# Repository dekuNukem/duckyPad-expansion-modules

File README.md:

# duckyPad Expansion Module

[Pre-order](https://www.kickstarter.com/projects/dekunukem/duckypad-pro-advanced-macro-scripting-beyond-qmk-via) | [Official Discord](https://discord.gg/4sJCBx5) | [Project Page](https://github.com/dekuNukem/duckyPad-Pro) | [Table of Contents](#table-of-contents)

duckyPad Expansion Module lets you wire up external **switches / buttons / foot pedals** to your duckyPad Pro.

* **8 Channels** Per Module

* **Daisy-Chain** up to 32 Channels

* USB-C Connector

## Table of Contents

- [Kit Assembly](#kit-assembly)
- [Connection Overview](#connection-overview)
	- [Terminal Block](#connection-terminal-block)
	- [3.5mm Audio Jack](#connection-35mm-audio-jack)
	- [Pin Headers](#connection-pin-headers)
- [Key Test](#key-test)
- [Configurator](#configurator)

## Kit Assembly

* **Wash your hands first** to discharge static electricity

You should have the following parts:

Insert the `8mm Screws` in `Bottom Plate`:

Place **something rigid** against the back, and flip over.

The screws should stay in place.

Put on **2.5mm Nylon Spacers**.

Insert the `Circuit Board`.

Then the `8mm Metal Spacer`

* **Moderately tighten** with a socket bit if available

* Avoid scratching the PCB or nearby components.

Leave the `Top Plate` off for now.

You can install it after everything is wired up.

## Back to duckyPad!

If you're just starting, **set up your duckyPad first by [following the User Guide](https://dekunukem.github.io/duckyPad-Pro/doc/getting_started.html)**

Play with scripts on built-in switches and encoders, continue here once familiarised.

## Connection Overview

**8 Channels** are available per module.

* Numbered 1 to 8
* A channel is **considered active** when it is **shorted to ground (GND)**.

Therefore, to wire up a switch, you just need to:

* Connect **one side** to **GND**
* And the **other side** to the **desired channel**

---------

You can make connections via:

* Terminal Block
* 3.5mm Jack
* Pin Headers

## Connection: Terminal Block

Take a look at the `terminal block`:

Contains **Channel 1 to 7** and **GND**

To wire up a switch, connect it between a channel and GND.

-------

As an example, here's a simple button with two wires:

* When not pushed, the wires are isolated.
* When pushed, they are **connected together**.

Therefore, we just need to attach one wire to GND, and the other to a channel.

* Flip up the lever for GND and the desired channel

* Strip around half inch / 1.2cm of conductor
* Insert into the hole
* Flip lever back down

## Connection: 3.5mm Audio Jack

Two 3.5mm TRS (Tip, Ring, Sleeve) connectors are available.

Sleeve is connected to GND.

Tip and Ring are connected to channels shown below.

## Connection: Pin Headers

All channels are also available on pin headers.

You can install a header or solder wires directly to them.

## Key Test

Use a USB-C cable and connect the module as shown.

* Make sure the `Towards duckyPad` marking faces duckyPad

* The other end is used for daisy-chaining

Press the `Key Test` script in `Welcome` profile

Press a built-in switch, the screen should respond.

Then activate a channel on the expansion module.

The corresponding LED should light up:

The screen should show too:

If so, congrats! Your wiring is correct.

## Configurator

You can assign actions to expansion channels just like any other key.

Module 1 is closest to duckyPad, up to 4 can be daisy-chained.

Some notes:

* If using a flip switch, select `Disable Auto-Repeat`.
* So the script doesn't repeat after changing state.

* Each channel can have different scripts for `onPress` and `onRelease`.
	* `onPress` is when a channel goes from inactive to active
	* `onRelase` is the opposite

## Questions or Comments?

Please feel free to [open an issue](https://github.com/dekuNukem/duckypad-pro/issues), ask in the [official duckyPad discord](https://discord.gg/4sJCBx5), or email `dekuNukem`@`gmail`.`com`!

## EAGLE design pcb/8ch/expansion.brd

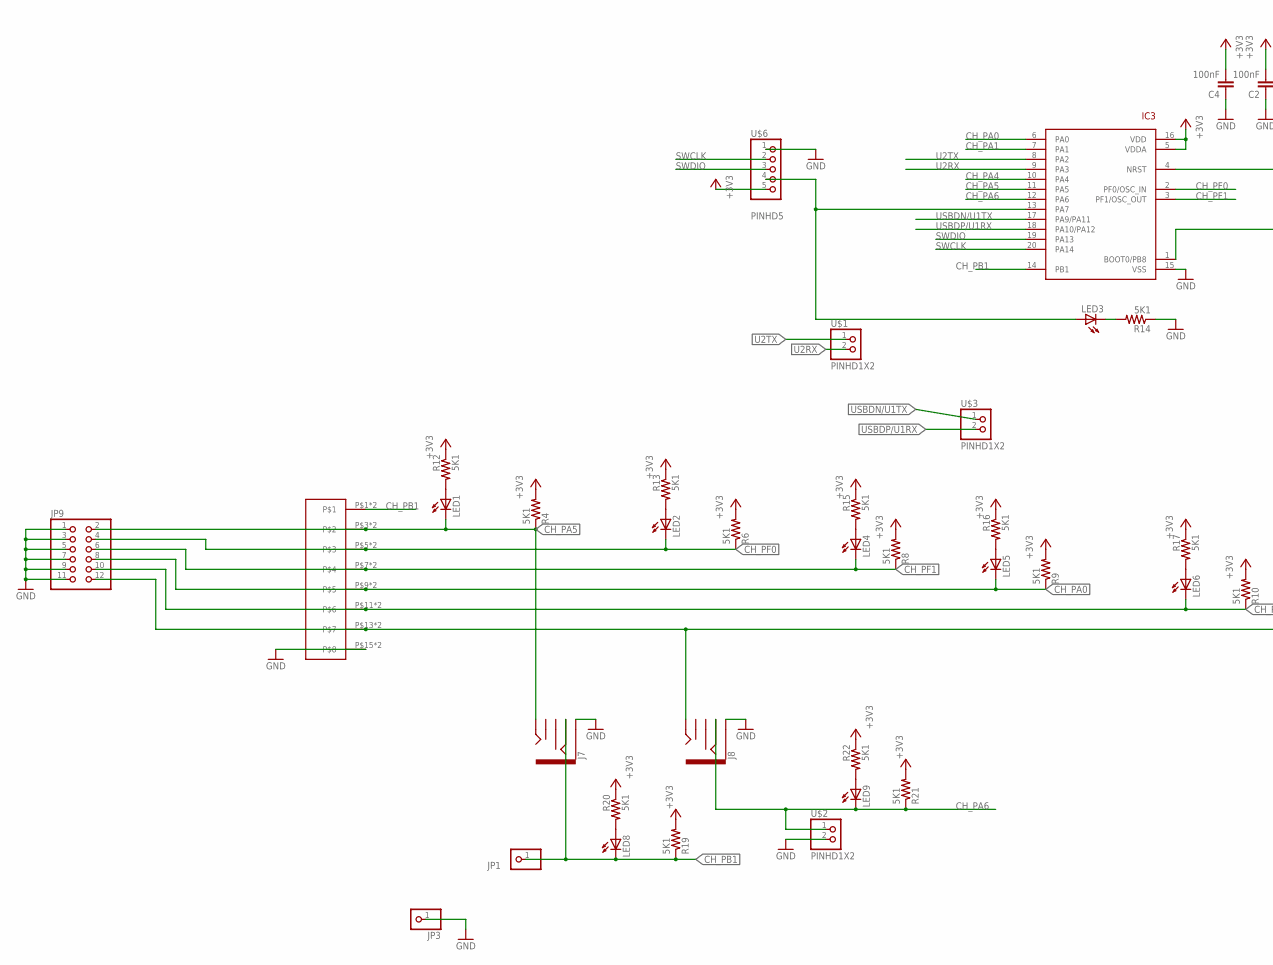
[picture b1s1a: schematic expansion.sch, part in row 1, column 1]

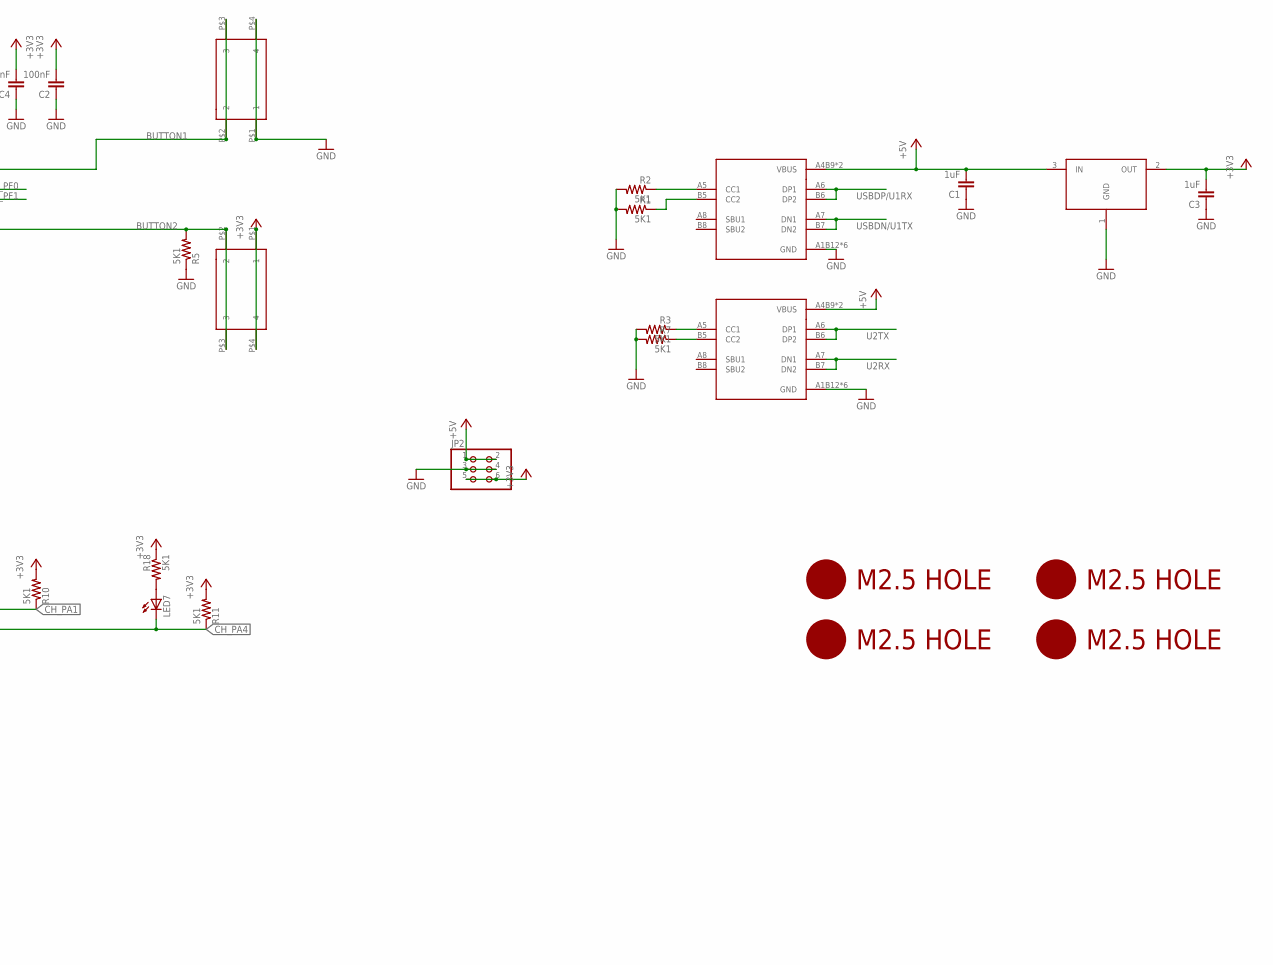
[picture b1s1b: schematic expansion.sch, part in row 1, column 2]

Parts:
C1, C3: 1uF; 0805
C2, C4: 100nF; 0805
IC3: STM32F042F4; TSSOP20
J7, J8: AUDIO_JACK_3.5MM_PTH; AUDIO-JACK
JP1, JP3: PINHD-1X1; 1X01
JP2: PINHD-2X3; 2X03
JP9: PINHD-2X6; 2X06
LED1, LED2, LED3, LED4, LED5, LED6, LED7, LED8, LED9: LEDCHIP-LED0805; CHIP-LED0805
R1, R2, R3, R4, R5, R6, R7, R8, R9, R10, R11, R12, R13, R14, R15, R16, R17, R18, R19, R20, R21, R22: 5K1; 0805
SW3, SW4: 324_SW; 342_SWICH_FOOT
U1, U2: USBC_16P; USBC_16P_FOOT
U4: XC6206_DEV; SOT23R_INFINEON
U$1, U$2, U$3: PINHD1X2; 1X02
U$6: PINHD5; 1X05
U$8, U$9, U$10, U$11: M2.5HOLE
U$14: DG2204R-5.0-8DG2204-8; DG2204R-8

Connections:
+3V3: C2.2, C3.2, C4.2, IC3.5 (VDDA), IC3.16 (VDD), JP2.5, JP2.6, R4.2, R6.2, R8.2, R9.2, R10.2, R11.2, R12.1, R13.1, R15.1, R16.1, R17.1, R18.1, R19.2, R20.1, R21.2, R22.1, SW4.P$1 (1), SW4.P$4 (4), U4.2 (OUT), U$6.5
+5V: C1.2, JP2.1, JP2.2, U1.A4B9 (VBUS), U1.B4A9 (VBUS), U2.A4B9 (VBUS), U2.B4A9 (VBUS), U4.3 (IN)
BUTTON1: IC3.4 (NRST), SW3.P$2 (2), SW3.P$3 (3)
BUTTON2: IC3.1 (BOOT0/PB8), R5.2, SW4.P$2 (2), SW4.P$3 (3)
CH_PA0: IC3.6 (PA0), JP9.8, LED5.C, R9.1, U$14.P$9, U$14.P$10
CH_PA1: IC3.7 (PA1), JP9.10, LED6.C, R10.1, U$14.P$11, U$14.P$12
CH_PA4: IC3.10 (PA4), J8.TIP, JP9.12, LED7.C, R11.1, U$14.P$13, U$14.P$14
CH_PA5: IC3.11 (PA5), J7.TIP, JP9.2, LED1.C, R4.1, U$14.P$3, U$14.P$4
CH_PA6: IC3.12 (PA6), J8.RING, LED9.C, R21.1, U$2.1
CH_PB1: IC3.14 (PB1), J7.RING, JP1.1, LED8.C, R19.1, U$14.P$1, U$14.P$2
CH_PF0: IC3.2 (PF0/OSC_IN), JP9.4, LED2.C, R6.1, U$14.P$5, U$14.P$6
CH_PF1: IC3.3 (PF1/OSC_OUT), JP9.6, LED4.C, R8.1, U$14.P$7, U$14.P$8
GND: C1.1, C2.1, C3.1, C4.1, IC3.15 (VSS), J7.SLEEVE, J8.SLEEVE, JP2.3, JP2.4, JP3.1, JP9.1, JP9.3, JP9.5, JP9.7, JP9.9, JP9.11, R1.2, R2.2, R3.2, R5.1, R7.2, R14.1, SW3.P$1 (1), SW3.P$4 (4), U1.A1B12 (GND), U1.B11A12 (GND), U1.P$13 (GND), U1.P$14 (GND), U1.P$15 (GND), U1.P$16 (GND), U2.A1B12 (GND), U2.B11A12 (GND), U2.P$13 (GND), U2.P$14 (GND), U2.P$15 (GND), U2.P$16 (GND), U4.1 (GND), U$2.2, U$6.1, U$14.P$15, U$14.P$16
unnamed: R3.1, U1.A5 (CC1)
unnamed: R7.1, U1.B5 (CC2)
unnamed: LED1.A, R12.2
unnamed: LED2.A, R13.2
unnamed: LED4.A, R15.2
unnamed: LED5.A, R16.2
unnamed: LED6.A, R17.2
unnamed: LED7.A, R18.2
unnamed: LED8.A, R20.2
unnamed: IC3.13 (PA7), LED3.A, U$6.4
unnamed: LED3.C, R14.2
unnamed: LED9.A, R22.2
unnamed: R1.1, U2.B5 (CC2)
unnamed: R2.1, U2.A5 (CC1)
SWCLK: IC3.20 (PA14), U$6.2
SWDIO: IC3.19 (PA13), U$6.3
U2RX: IC3.9 (PA3), U1.A7 (DN1), U1.B7 (DN2), U$1.2
U2TX: IC3.8 (PA2), U1.A6 (DP1), U1.B6 (DP2), U$1.1
USBDN/U1TX: IC3.17 (PA9/PA11), U2.A7 (DN1), U2.B7 (DN2), U$3.1
USBDP/U1RX: IC3.18 (PA10/PA12), U2.A6 (DP1), U2.B6 (DP2), U$3.2

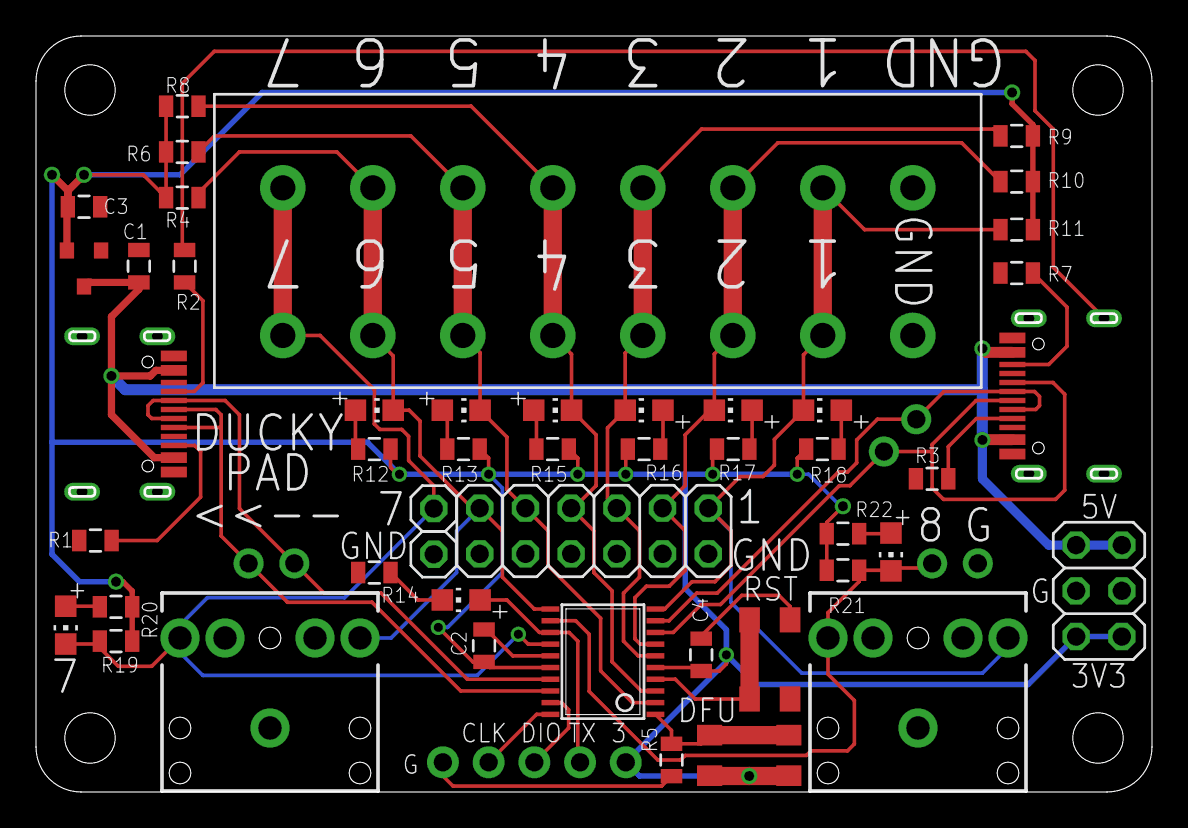
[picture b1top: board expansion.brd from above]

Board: 2 copper layers, 61.8 x 41.8 mm, 56 parts (0 on the bottom side), 33 nets.

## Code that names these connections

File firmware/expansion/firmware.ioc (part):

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Mcu.Name=STM32F042F6Px
Mcu.Package=TSSOP20
Mcu.UserName=STM32F042F6Px
PA0.GPIOParameters=GPIO_PuPd,GPIO_Label
PA0.GPIO_Label=CH3
PA0.GPIO_PuPd=GPIO_PULLUP
PA0.Signal=GPIO_Input
PA1.GPIOParameters=GPIO_PuPd,GPIO_Label
PA1.GPIO_Label=CH2
PA1.GPIO_PuPd=GPIO_PULLUP
PA1.Signal=GPIO_Input
PA10.Mode=Asynchronous
PA10.Signal=USART1_RX
PA13.Mode=Serial_Wire
PA13.Signal=SYS_SWDIO
PA14.Mode=Serial_Wire
PA14.Signal=SYS_SWCLK
PA2.Mode=Asynchronous
PA2.Signal=USART2_TX
PA3.Mode=Asynchronous
PA3.Signal=USART2_RX
PA4.GPIOParameters=GPIO_PuPd,GPIO_Label
PA4.GPIO_Label=CH1
PA4.GPIO_PuPd=GPIO_PULLUP
PA4.Signal=GPIO_Input
PA5.GPIOParameters=GPIO_PuPd,GPIO_Label
PA5.GPIO_Label=CH6
PA5.GPIO_PuPd=GPIO_PULLUP
PA5.Signal=GPIO_Input
PA6.GPIOParameters=GPIO_PuPd,GPIO_Label
PA6.GPIO_Label=CH8
PA6.GPIO_PuPd=GPIO_PULLUP
PA6.Signal=GPIO_Input
PA7.GPIOParameters=GPIO_Label
PA7.GPIO_Label=SSTX_USERLED
PA7.Signal=GPIO_Output
PA9.Mode=Asynchronous
PA9.Signal=USART1_TX
PB1.GPIOParameters=GPIO_PuPd,GPIO_Label
PB1.GPIO_Label=CH7
PB1.GPIO_PuPd=GPIO_PULLUP
PB1.Signal=GPIO_Input
PB8.GPIOParameters=GPIO_Label
PB8.GPIO_Label=USER_BUTTON
PB8.Signal=GPIO_Input
PF0-OSC_IN.GPIOParameters=GPIO_PuPd,GPIO_Label
PF0-OSC_IN.GPIO_Label=CH5
PF0-OSC_IN.GPIO_PuPd=GPIO_PULLUP
PF0-OSC_IN.Signal=GPIO_Input
PF1-OSC_OUT.GPIOParameters=GPIO_PuPd,GPIO_Label
PF1-OSC_OUT.GPIO_Label=CH4
PF1-OSC_OUT.GPIO_PuPd=GPIO_PULLUP
PF1-OSC_OUT.Signal=GPIO_Input
RCC.SYSCLKFreq_VALUE=48000000
RCC.SYSCLKSource=RCC_SYSCLKSOURCE_HSI48
board=custom

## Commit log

2024-08-24 commented out some printf
2024-09-16 writing
2024-09-16 added svg
2024-10-09 working on new PCB
2024-10-09 finishing touch
2024-10-15 added PB1 LED
2024-10-15 added 2 aux channels, cleanup
2024-10-15 moved channel 7 to terminal and on header
2024-10-15 silkscreen cleanup
2024-10-15 adjusted firmware for 8ch
2024-10-18 updated fw
2024-10-18 finishing touches
2024-10-19 added dimension drawings
2024-11-04 making cover plates
2024-11-04 added plate gerber
2024-11-21 writing doc
2024-12-12 adjusted silkscreen
2024-12-12 added more detailed instruction about audio jack and pin headers
2024-12-12 adjust wording
2024-12-12 fix typo
2024-12-20 updated TRS image
2024-12-20 added main user guide

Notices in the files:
parts and their libraries:
SparkFun-Passives: Licensing: Creative Commons ShareAlike 4.0 International - https://creativecommons.org/licenses/by-sa/4.0
